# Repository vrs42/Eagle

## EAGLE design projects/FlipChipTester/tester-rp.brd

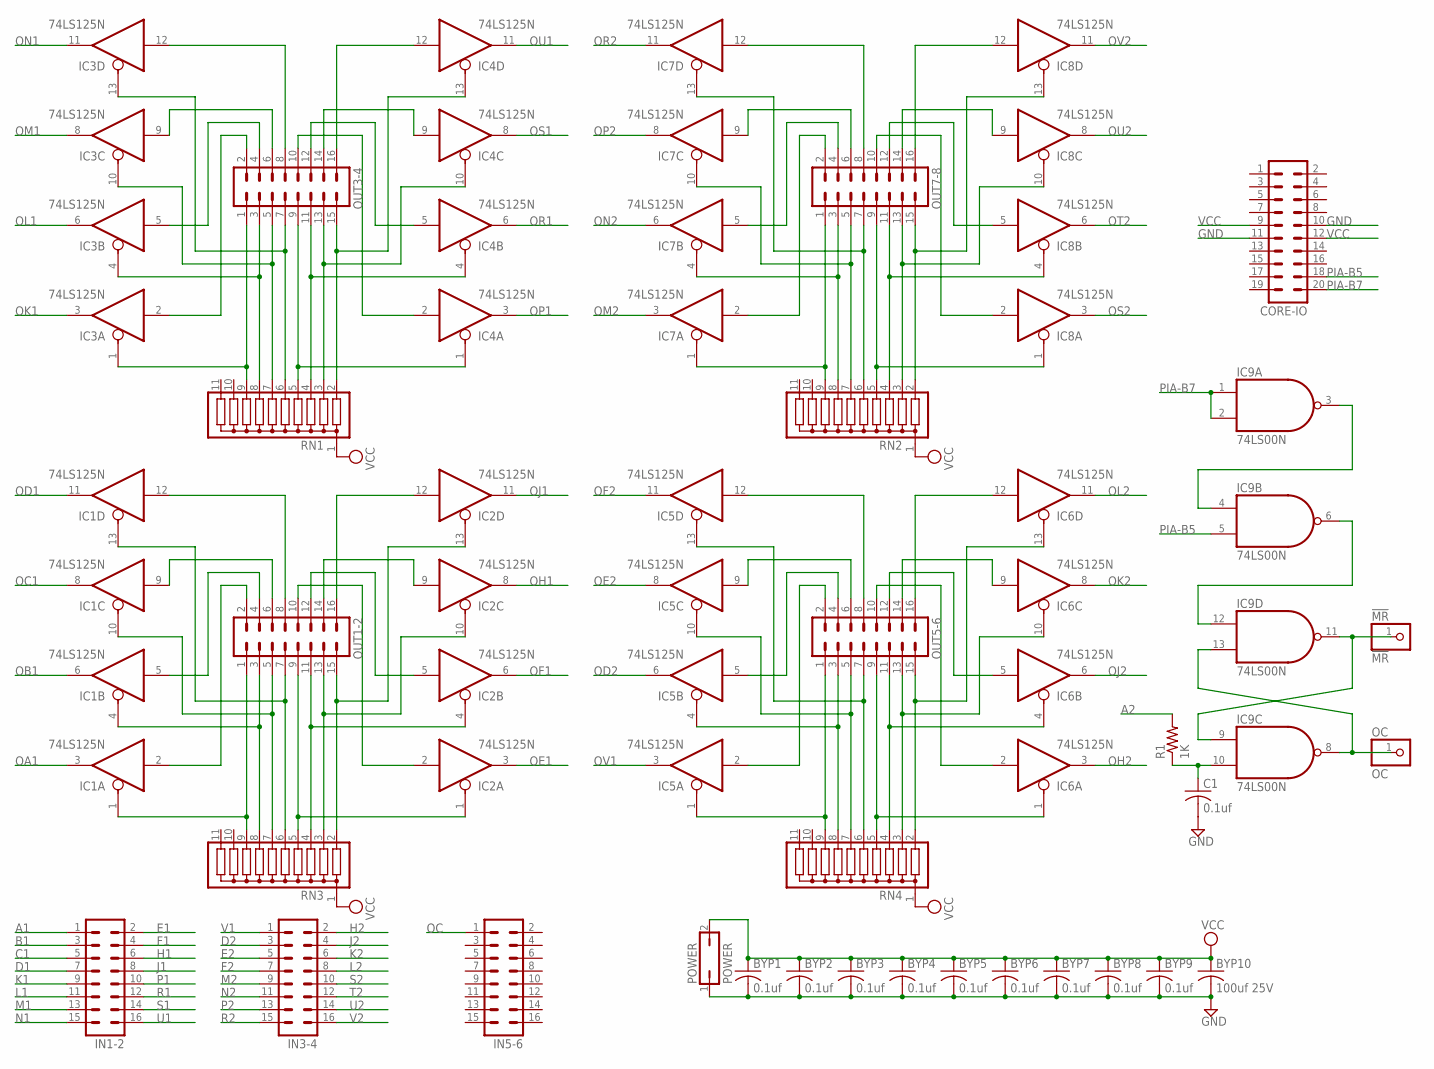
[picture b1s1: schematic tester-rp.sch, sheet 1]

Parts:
!MR: !MR; 1X01
BYP1, BYP2, BYP3, BYP4, BYP5, BYP6, BYP7, BYP8, BYP9: 0.1uf; C050-025X075
BYP10: 100uf 25V; C150-064X183
C1: 0.1uf; C050-025X075
CORE-IO: MA10-2
IC1, IC2, IC3, IC4, IC5, IC6, IC7, IC8: 74LS125N; DIL14
IC9: 74LS00N; DIL14
IN1-2, IN3-4, IN5-6: MA08-2
OC: OC; 1X01
OUT1-2, OUT3-4, OUT5-6, OUT7-8: MA08-2
POWER: POWER; JP1
R1: 1K; 0207/10
RN1, RN2, RN3, RN4: G10R; SIL11

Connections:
!MR: !MR.1, IC9.9 (I0), IC9.11 (O)
A1: IN1-2.1; also elsewhere on the board
A2: R1.2; also elsewhere on the board
B1: IN1-2.3; also elsewhere on the board
C1: IN1-2.5; also elsewhere on the board
D1: IN1-2.7; also elsewhere on the board
D2: IN3-4.3; also elsewhere on the board
E1: IN1-2.2; also elsewhere on the board
E2: IN3-4.5; also elsewhere on the board
F1: IN1-2.4; also elsewhere on the board
F2: IN3-4.7; also elsewhere on the board
GND: BYP1.2, BYP2.2, BYP3.2, BYP4.2, BYP5.2, BYP6.2, BYP7.2, BYP8.2, BYP9.2, BYP10.2, C1.2, CORE-IO.10, CORE-IO.11, IC1.7 (GND), IC2.7 (GND), IC3.7 (GND), IC4.7 (GND), IC5.7 (GND), IC6.7 (GND), IC7.7 (GND), IC8.7 (GND), IC9.7 (GND), POWER.1; also elsewhere on the board
H1: IN1-2.6; also elsewhere on the board
H2: IN3-4.2; also elsewhere on the board
J1: IN1-2.8; also elsewhere on the board
J2: IN3-4.4; also elsewhere on the board
K1: IN1-2.9; also elsewhere on the board
K2: IN3-4.6; also elsewhere on the board
L1: IN1-2.11; also elsewhere on the board
L2: IN3-4.8; also elsewhere on the board
M1: IN1-2.13; also elsewhere on the board
M2: IN3-4.9; also elsewhere on the board
N1: IN1-2.15; also elsewhere on the board
N2: IN3-4.11; also elsewhere on the board
unnamed: IC9.6 (O), IC9.12 (I0)
unnamed: IC9.3 (O), IC9.4 (I0)
unnamed: C1.1, IC9.10 (I1), R1.1
unnamed: IC1.1 (OE), OUT1-2.1, RN3.9
unnamed: IC1.4 (OE), OUT1-2.3, RN3.8
unnamed: IC1.10 (OE), OUT1-2.5, RN3.7
unnamed: IC1.13 (OE), OUT1-2.7, RN3.6
unnamed: IC1.2 (I), OUT1-2.2
unnamed: IC1.5 (I), OUT1-2.4
unnamed: IC1.9 (I), OUT1-2.6
unnamed: IC1.12 (I), OUT1-2.8
unnamed: IC5.4 (OE), OUT5-6.3, RN4.8
unnamed: IC2.10 (OE), OUT1-2.13, RN3.3
unnamed: IC2.4 (OE), OUT1-2.11, RN3.4
unnamed: IC2.1 (OE), OUT1-2.9, RN3.5
unnamed: IC2.2 (I), OUT1-2.10
unnamed: IC2.5 (I), OUT1-2.12
unnamed: IC2.9 (I), OUT1-2.14
unnamed: IC2.12 (I), OUT1-2.16
unnamed: IC5.13 (OE), OUT5-6.7, RN4.6
unnamed: IC2.13 (OE), OUT1-2.15, RN3.2
unnamed: IC5.2 (I), OUT5-6.2
unnamed: IC5.5 (I), OUT5-6.4
unnamed: IC5.9 (I), OUT5-6.6
unnamed: IC5.12 (I), OUT5-6.8
unnamed: IC6.10 (OE), OUT5-6.13, RN4.3
unnamed: IC6.4 (OE), OUT5-6.11, RN4.4
unnamed: IC6.1 (OE), OUT5-6.9, RN4.5
unnamed: IC6.2 (I), OUT5-6.10
unnamed: IC6.9 (I), OUT5-6.14
unnamed: IC6.12 (I), OUT5-6.16
unnamed: IC5.1 (OE), OUT5-6.1, RN4.9
unnamed: IC5.10 (OE), OUT5-6.5, RN4.7
unnamed: IC6.5 (I), OUT5-6.12
unnamed: IC6.13 (OE), OUT5-6.15, RN4.2
unnamed: IC3.4 (OE), OUT3-4.3, RN1.8
unnamed: IC3.13 (OE), OUT3-4.7, RN1.6
unnamed: IC3.2 (I), OUT3-4.2
unnamed: IC3.5 (I), OUT3-4.4
unnamed: IC3.9 (I), OUT3-4.6
unnamed: IC3.12 (I), OUT3-4.8
unnamed: IC4.10 (OE), OUT3-4.13, RN1.3
unnamed: IC4.4 (OE), OUT3-4.11, RN1.4
unnamed: IC4.1 (OE), OUT3-4.9, RN1.5
unnamed: IC4.2 (I), OUT3-4.10
unnamed: IC4.9 (I), OUT3-4.14
unnamed: IC4.12 (I), OUT3-4.16
unnamed: IC3.1 (OE), OUT3-4.1, RN1.9
unnamed: IC3.10 (OE), OUT3-4.5, RN1.7
unnamed: IC4.5 (I), OUT3-4.12
unnamed: IC4.13 (OE), OUT3-4.15, RN1.2
unnamed: IC7.4 (OE), OUT7-8.3, RN2.8
unnamed: IC7.13 (OE), OUT7-8.7, RN2.6
unnamed: IC7.2 (I), OUT7-8.2
unnamed: IC7.5 (I), OUT7-8.4
unnamed: IC7.9 (I), OUT7-8.6
unnamed: IC7.12 (I), OUT7-8.8
unnamed: IC8.10 (OE), OUT7-8.13, RN2.3
unnamed: IC8.4 (OE), OUT7-8.11, RN2.4
unnamed: IC8.1 (OE), OUT7-8.9, RN2.5
unnamed: IC8.2 (I), OUT7-8.10
unnamed: IC8.9 (I), OUT7-8.14
unnamed: IC8.12 (I), OUT7-8.16
unnamed: IC7.1 (OE), OUT7-8.1, RN2.9
unnamed: IC7.10 (OE), OUT7-8.5, RN2.7
unnamed: IC8.5 (I), OUT7-8.12
unnamed: IC8.13 (OE), OUT7-8.15, RN2.2
OA1: IC1.3 (O); also elsewhere on the board
OB1: IC1.6 (O); also elsewhere on the board
OC: IC9.8 (O), IC9.13 (I1), IN5-6.1, OC.1
OC1: IC1.8 (O); also elsewhere on the board
OD1: IC1.11 (O); also elsewhere on the board
OD2: IC5.6 (O); also elsewhere on the board
OE1: IC2.3 (O); also elsewhere on the board
OE2: IC5.8 (O); also elsewhere on the board
OF1: IC2.6 (O); also elsewhere on the board
OF2: IC5.11 (O); also elsewhere on the board
OH1: IC2.8 (O); also elsewhere on the board
OH2: IC6.3 (O); also elsewhere on the board
OJ1: IC2.11 (O); also elsewhere on the board
OJ2: IC6.6 (O); also elsewhere on the board
OK1: IC3.3 (O); also elsewhere on the board
OK2: IC6.8 (O); also elsewhere on the board
OL1: IC3.6 (O); also elsewhere on the board
OL2: IC6.11 (O); also elsewhere on the board
OM1: IC3.8 (O); also elsewhere on the board
OM2: IC7.3 (O); also elsewhere on the board
ON1: IC3.11 (O); also elsewhere on the board
ON2: IC7.6 (O); also elsewhere on the board
OP1: IC4.3 (O); also elsewhere on the board
OP2: IC7.8 (O); also elsewhere on the board
OR1: IC4.6 (O); also elsewhere on the board
OR2: IC7.11 (O); also elsewhere on the board
OS1: IC4.8 (O); also elsewhere on the board
OS2: IC8.3 (O); also elsewhere on the board
OT2: IC8.6 (O); also elsewhere on the board
OU1: IC4.11 (O); also elsewhere on the board
OU2: IC8.8 (O); also elsewhere on the board
OV1: IC5.3 (O); also elsewhere on the board
OV2: IC8.11 (O); also elsewhere on the board
P1: IN1-2.10; also elsewhere on the board
P2: IN3-4.13; also elsewhere on the board
PIA-B5: CORE-IO.18, IC9.5 (I1)
PIA-B7: CORE-IO.20, IC9.1 (I0), IC9.2 (I1)
R1: IN1-2.12; also elsewhere on the board
R2: IN3-4.15; also elsewhere on the board
S1: IN1-2.14; also elsewhere on the board
S2: IN3-4.10; also elsewhere on the board
T2: IN3-4.12; also elsewhere on the board
U1: IN1-2.16; also elsewhere on the board
U2: IN3-4.14; also elsewhere on the board
V1: IN3-4.1; also elsewhere on the board
V2: IN3-4.16; also elsewhere on the board
VCC: BYP1.1, BYP2.1, BYP3.1, BYP4.1, BYP5.1, BYP6.1, BYP7.1, BYP8.1, BYP9.1, BYP10.1, CORE-IO.9, CORE-IO.12, IC1.14 (VCC), IC2.14 (VCC), IC3.14 (VCC), IC4.14 (VCC), IC5.14 (VCC), IC6.14 (VCC), IC7.14 (VCC), IC8.14 (VCC), IC9.14 (VCC), POWER.2, RN1.1, RN2.1, RN3.1, RN4.1; also elsewhere on the board

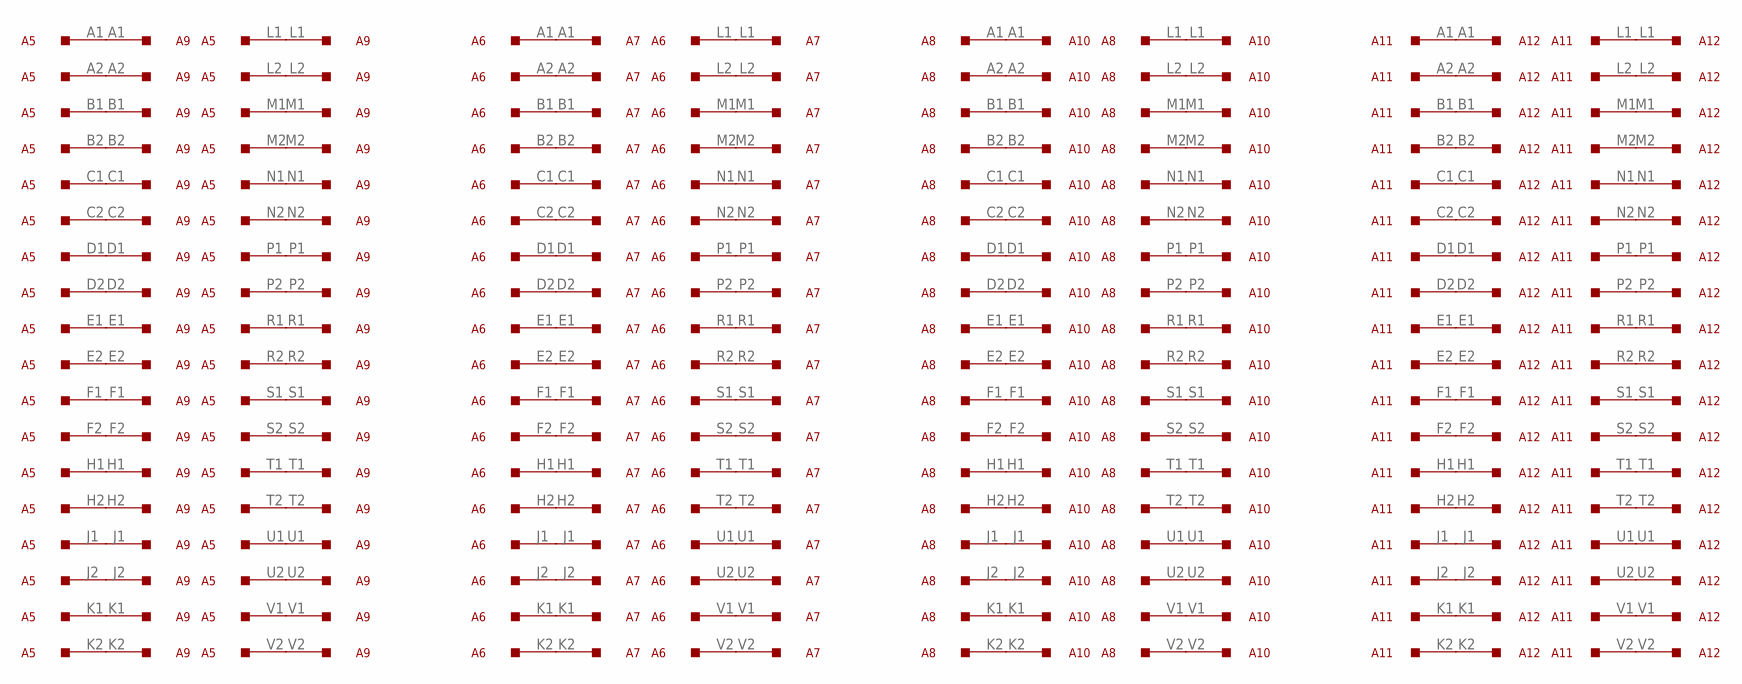
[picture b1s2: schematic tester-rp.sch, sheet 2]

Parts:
A5, A6, A7, A8, A9, A10, A11, A12: M916; H807

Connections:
unnamed: A5.L1, A9.L1
unnamed: A5.L2, A9.L2
unnamed: A5.M1, A9.M1
unnamed: A5.M2, A9.M2
unnamed: A5.N1, A9.N1
unnamed: A5.N2, A9.N2
unnamed: A5.P1, A9.P1
unnamed: A5.P2, A9.P2
unnamed: A5.R1, A9.R1
unnamed: A5.R2, A9.R2
unnamed: A5.S1, A9.S1
unnamed: A5.S2, A9.S2
unnamed: A5.T1, A9.T1
unnamed: A5.T2, A9.T2
unnamed: A5.U1, A9.U1
unnamed: A5.U2, A9.U2
unnamed: A5.V1, A9.V1
unnamed: A5.V2, A9.V2
unnamed: A5.A1, A9.A1
unnamed: A5.A2, A9.A2
unnamed: A5.B1, A9.B1
unnamed: A5.B2, A9.B2
unnamed: A5.C1, A9.C1
unnamed: A5.C2, A9.C2
unnamed: A5.D1, A9.D1
unnamed: A5.D2, A9.D2
unnamed: A5.E1, A9.E1
unnamed: A5.E2, A9.E2
unnamed: A5.F1, A9.F1
unnamed: A5.F2, A9.F2
unnamed: A5.H1, A9.H1
unnamed: A5.H2, A9.H2
unnamed: A5.J1, A9.J1
unnamed: A5.J2, A9.J2
unnamed: A5.K1, A9.K1
unnamed: A5.K2, A9.K2
unnamed: A6.L1, A7.L1
unnamed: A6.L2, A7.L2
unnamed: A6.M1, A7.M1
unnamed: A6.M2, A7.M2
unnamed: A6.N1, A7.N1
unnamed: A6.N2, A7.N2
unnamed: A6.P1, A7.P1
unnamed: A6.P2, A7.P2
unnamed: A6.R1, A7.R1
unnamed: A6.R2, A7.R2
unnamed: A6.S1, A7.S1
unnamed: A6.S2, A7.S2
unnamed: A6.T1, A7.T1
unnamed: A6.T2, A7.T2
unnamed: A6.U1, A7.U1
unnamed: A6.U2, A7.U2
unnamed: A6.V1, A7.V1
unnamed: A6.V2, A7.V2
unnamed: A6.A1, A7.A1
unnamed: A6.A2, A7.A2
unnamed: A6.B1, A7.B1
unnamed: A6.B2, A7.B2
unnamed: A6.C1, A7.C1
unnamed: A6.C2, A7.C2
unnamed: A6.D1, A7.D1
unnamed: A6.D2, A7.D2
unnamed: A6.E1, A7.E1
unnamed: A6.E2, A7.E2
unnamed: A6.F1, A7.F1
unnamed: A6.F2, A7.F2
unnamed: A6.H1, A7.H1
unnamed: A6.H2, A7.H2
unnamed: A6.J1, A7.J1
unnamed: A6.J2, A7.J2
unnamed: A6.K1, A7.K1
unnamed: A6.K2, A7.K2
unnamed: A8.L1, A10.L1
unnamed: A8.L2, A10.L2
unnamed: A8.M1, A10.M1
unnamed: A8.M2, A10.M2
unnamed: A8.N1, A10.N1
unnamed: A8.N2, A10.N2
unnamed: A8.P1, A10.P1
unnamed: A8.P2, A10.P2
unnamed: A8.R1, A10.R1
unnamed: A8.R2, A10.R2
unnamed: A8.S1, A10.S1
unnamed: A8.S2, A10.S2
unnamed: A8.T1, A10.T1
unnamed: A8.T2, A10.T2
unnamed: A8.U1, A10.U1
unnamed: A8.U2, A10.U2
unnamed: A8.V1, A10.V1
unnamed: A8.V2, A10.V2
unnamed: A8.A1, A10.A1
unnamed: A8.A2, A10.A2
unnamed: A8.B1, A10.B1
unnamed: A8.B2, A10.B2
unnamed: A8.C1, A10.C1
unnamed: A8.C2, A10.C2
unnamed: A8.D1, A10.D1
unnamed: A8.D2, A10.D2
unnamed: A8.E1, A10.E1
unnamed: A8.E2, A10.E2
unnamed: A8.F1, A10.F1
unnamed: A8.F2, A10.F2
unnamed: A8.H1, A10.H1
unnamed: A8.H2, A10.H2
unnamed: A8.J1, A10.J1
unnamed: A8.J2, A10.J2
unnamed: A8.K1, A10.K1
unnamed: A8.K2, A10.K2
unnamed: A11.L1, A12.L1
unnamed: A11.L2, A12.L2
unnamed: A11.M1, A12.M1
unnamed: A11.M2, A12.M2
unnamed: A11.N1, A12.N1
unnamed: A11.N2, A12.N2
unnamed: A11.P1, A12.P1
unnamed: A11.P2, A12.P2
unnamed: A11.R1, A12.R1
unnamed: A11.R2, A12.R2
unnamed: A11.S1, A12.S1
unnamed: A11.S2, A12.S2
unnamed: A11.T1, A12.T1
unnamed: A11.T2, A12.T2
unnamed: A11.U1, A12.U1
unnamed: A11.U2, A12.U2
unnamed: A11.V1, A12.V1
unnamed: A11.V2, A12.V2
unnamed: A11.A1, A12.A1
unnamed: A11.A2, A12.A2
unnamed: A11.B1, A12.B1
unnamed: A11.B2, A12.B2
unnamed: A11.C1, A12.C1
unnamed: A11.C2, A12.C2
unnamed: A11.D1, A12.D1
unnamed: A11.D2, A12.D2
unnamed: A11.E1, A12.E1
unnamed: A11.E2, A12.E2
unnamed: A11.F1, A12.F1
unnamed: A11.F2, A12.F2
unnamed: A11.H1, A12.H1
unnamed: A11.H2, A12.H2
unnamed: A11.J1, A12.J1
unnamed: A11.J2, A12.J2
unnamed: A11.K1, A12.K1
unnamed: A11.K2, A12.K2

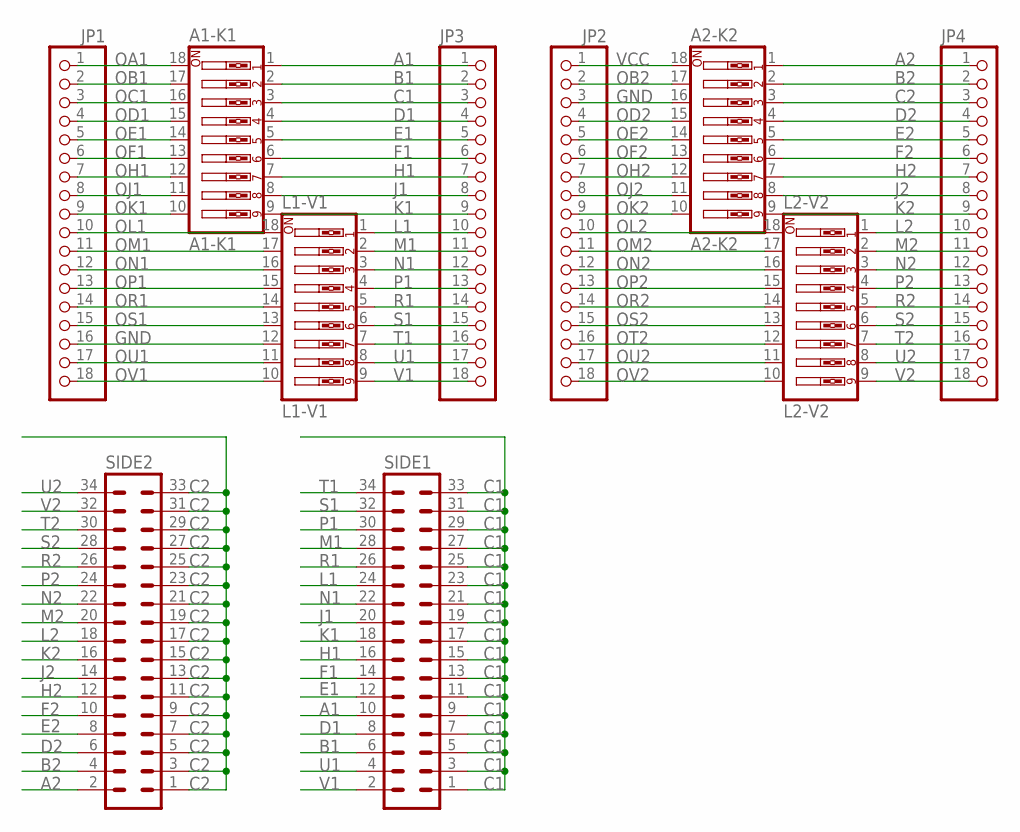
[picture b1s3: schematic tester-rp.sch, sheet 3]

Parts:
A1-K1: A1-K1; EDG-09
A2-K2: A2-K2; EDG-09
JP1, JP2, JP3, JP4: PINHD-1X18; 1X18
L1-V1: L1-V1; EDG-09
L2-V2: L2-V2; EDG-09
SIDE1, SIDE2: MA17-2

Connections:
A1: A1-K1.1, JP3.1, SIDE1.10; also elsewhere on the board
A2: A2-K2.1, JP4.1, SIDE2.2; also elsewhere on the board
B1: A1-K1.2, JP3.2, SIDE1.6; also elsewhere on the board
B2: A2-K2.2, JP4.2, SIDE2.4
C1: A1-K1.3, JP3.3, SIDE1.1, SIDE1.3, SIDE1.5, SIDE1.7, SIDE1.9, SIDE1.11, SIDE1.13, SIDE1.15, SIDE1.17, SIDE1.19, SIDE1.21, SIDE1.23, SIDE1.25, SIDE1.27, SIDE1.29, SIDE1.31, SIDE1.33; also elsewhere on the board
C2: A2-K2.3, JP4.3, SIDE2.1, SIDE2.3, SIDE2.5, SIDE2.7, SIDE2.9, SIDE2.11, SIDE2.13, SIDE2.15, SIDE2.17, SIDE2.19, SIDE2.21, SIDE2.23, SIDE2.25, SIDE2.27, SIDE2.29, SIDE2.31, SIDE2.33
D1: A1-K1.4, JP3.4, SIDE1.8; also elsewhere on the board
D2: A2-K2.4, JP4.4, SIDE2.6; also elsewhere on the board
E1: A1-K1.5, JP3.5, SIDE1.12; also elsewhere on the board
E2: A2-K2.5, JP4.5, SIDE2.8; also elsewhere on the board
F1: A1-K1.6, JP3.6, SIDE1.14; also elsewhere on the board
F2: A2-K2.6, JP4.6, SIDE2.10; also elsewhere on the board
GND: A2-K2.16, JP1.16, JP2.3, L1-V1.12; also elsewhere on the board
H1: A1-K1.7, JP3.7, SIDE1.16; also elsewhere on the board
H2: A2-K2.7, JP4.7, SIDE2.12; also elsewhere on the board
J1: A1-K1.8, JP3.8, SIDE1.20; also elsewhere on the board
J2: A2-K2.8, JP4.8, SIDE2.14; also elsewhere on the board
K1: A1-K1.9, JP3.9, SIDE1.18; also elsewhere on the board
K2: A2-K2.9, JP4.9, SIDE2.16; also elsewhere on the board
L1: JP3.10, L1-V1.1, SIDE1.24; also elsewhere on the board
L2: JP4.10, L2-V2.1, SIDE2.18; also elsewhere on the board
M1: JP3.11, L1-V1.2, SIDE1.28; also elsewhere on the board
M2: JP4.11, L2-V2.2, SIDE2.20; also elsewhere on the board
N1: JP3.12, L1-V1.3, SIDE1.22; also elsewhere on the board
N2: JP4.12, L2-V2.3, SIDE2.22; also elsewhere on the board
OA1: A1-K1.18, JP1.1; also elsewhere on the board
OB1: A1-K1.17, JP1.2; also elsewhere on the board
OB2: A2-K2.17, JP2.2
OC1: A1-K1.16, JP1.3; also elsewhere on the board
OD1: A1-K1.15, JP1.4; also elsewhere on the board
OD2: A2-K2.15, JP2.4; also elsewhere on the board
OE1: A1-K1.14, JP1.5; also elsewhere on the board
OE2: A2-K2.14, JP2.5; also elsewhere on the board
OF1: A1-K1.13, JP1.6; also elsewhere on the board
OF2: A2-K2.13, JP2.6; also elsewhere on the board
OH1: A1-K1.12, JP1.7; also elsewhere on the board
OH2: A2-K2.12, JP2.7; also elsewhere on the board
OJ1: A1-K1.11, JP1.8; also elsewhere on the board
OJ2: A2-K2.11, JP2.8; also elsewhere on the board
OK1: A1-K1.10, JP1.9; also elsewhere on the board
OK2: A2-K2.10, JP2.9; also elsewhere on the board
OL1: JP1.10, L1-V1.18; also elsewhere on the board
OL2: JP2.10, L2-V2.18; also elsewhere on the board
OM1: JP1.11, L1-V1.17; also elsewhere on the board
OM2: JP2.11, L2-V2.17; also elsewhere on the board
ON1: JP1.12, L1-V1.16; also elsewhere on the board
ON2: JP2.12, L2-V2.16; also elsewhere on the board
OP1: JP1.13, L1-V1.15; also elsewhere on the board
OP2: JP2.13, L2-V2.15; also elsewhere on the board
OR1: JP1.14, L1-V1.14; also elsewhere on the board
OR2: JP2.14, L2-V2.14; also elsewhere on the board
OS1: JP1.15, L1-V1.13; also elsewhere on the board
OS2: JP2.15, L2-V2.13; also elsewhere on the board
OT2: JP2.16, L2-V2.12; also elsewhere on the board
OU1: JP1.17, L1-V1.11; also elsewhere on the board
OU2: JP2.17, L2-V2.11; also elsewhere on the board
OV1: JP1.18, L1-V1.10; also elsewhere on the board
OV2: JP2.18, L2-V2.10; also elsewhere on the board
P1: JP3.13, L1-V1.4, SIDE1.30; also elsewhere on the board
P2: JP4.13, L2-V2.4, SIDE2.24; also elsewhere on the board
R1: JP3.14, L1-V1.5, SIDE1.26; also elsewhere on the board
R2: JP4.14, L2-V2.5, SIDE2.26; also elsewhere on the board
S1: JP3.15, L1-V1.6, SIDE1.32; also elsewhere on the board
S2: JP4.15, L2-V2.6, SIDE2.28; also elsewhere on the board
T1: JP3.16, L1-V1.7, SIDE1.34
T2: JP4.16, L2-V2.7, SIDE2.30; also elsewhere on the board
U1: JP3.17, L1-V1.8, SIDE1.4; also elsewhere on the board
U2: JP4.17, L2-V2.8, SIDE2.34; also elsewhere on the board
V1: JP3.18, L1-V1.9, SIDE1.2; also elsewhere on the board
V2: JP4.18, L2-V2.9, SIDE2.32; also elsewhere on the board
VCC: A2-K2.18, JP2.1; also elsewhere on the board

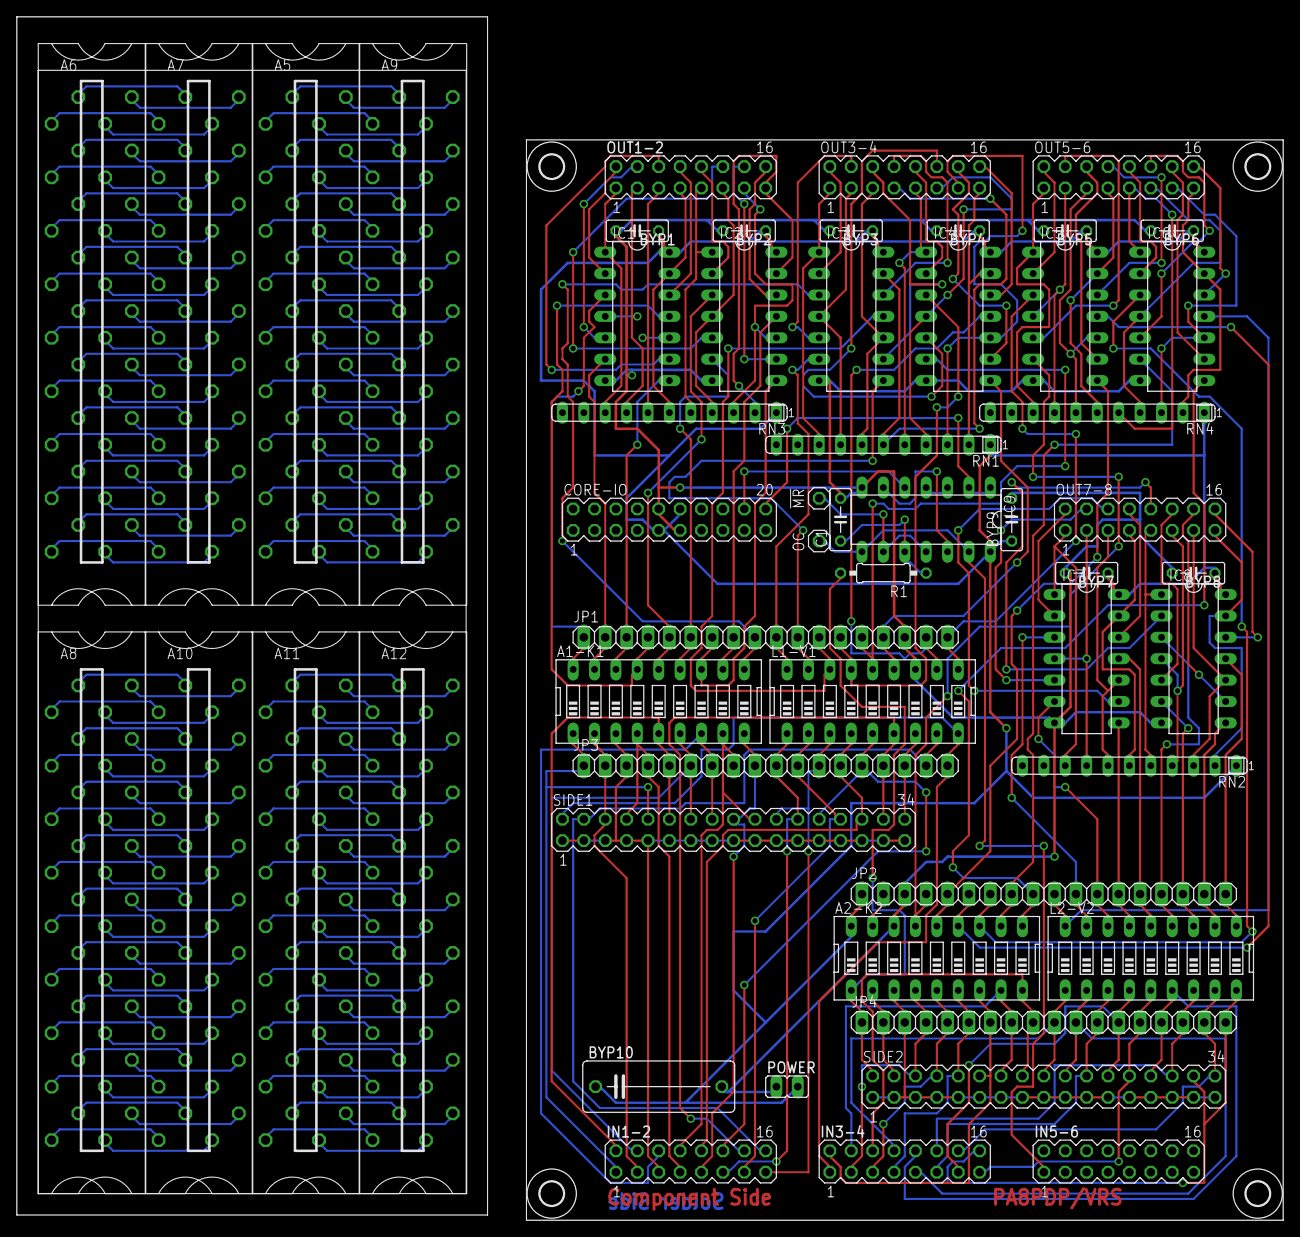
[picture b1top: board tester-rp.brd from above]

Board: 2 copper layers, 89.8 x 128.2 mm, 59 parts (0 on the bottom side), 286 nets.

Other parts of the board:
U$1, U$2, U$3, U$4: 2,8
U$5: CBLOCK

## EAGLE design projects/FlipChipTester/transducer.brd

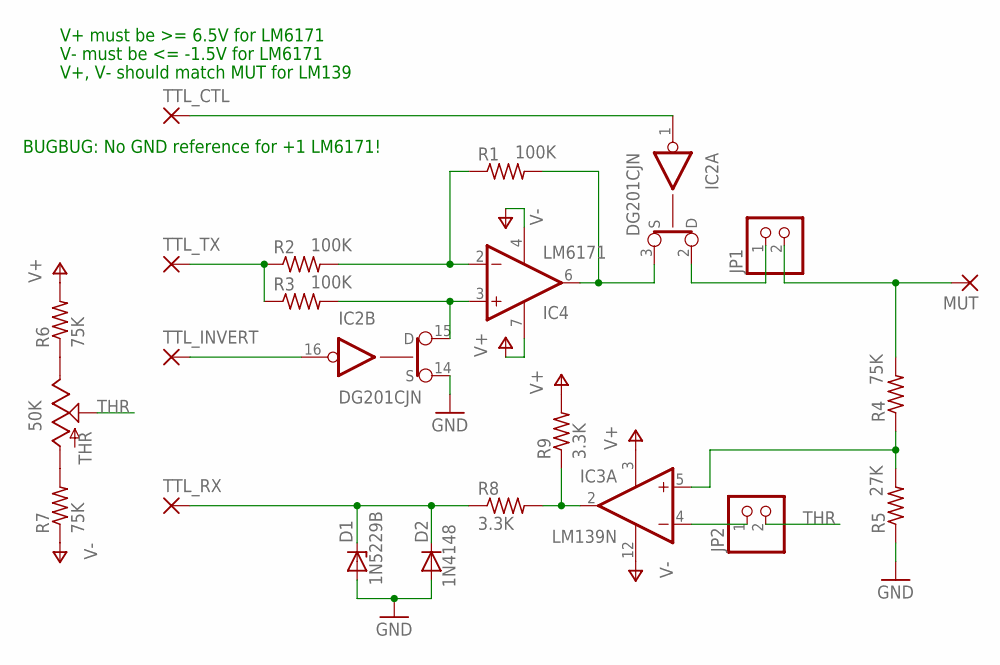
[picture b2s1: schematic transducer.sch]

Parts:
D1: 1N5229B; DO35Z10
D2: 1N4148; DO35-10
IC2: DG201CJN; DIL16
IC3: LM139N; DIL14
IC4: LM6171; DIL08
JP1, JP2: PINHD-1X2; 1X02
MUT: 1,6/0,9
R1, R2, R3: 100K; 0207/10
R4, R6, R7: 75K; 0207/10
R5: 27K; 0207/10
R8, R9: 3.3K; 0207/10
THR: 50K; SP19L
TTL_CTL: 1,6/0,9
TTL_INVERT: 1,6/0,9
TTL_RX: 1,6/0,9
TTL_TX: 1,6/0,9

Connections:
GND: D1.A, D2.A, IC2.5 (GND), IC2.14 (S), R5.1
unnamed: R2.1, R3.1, TTL_TX.1
unnamed: IC2.15 (D), IC4.3 (+IN), R3.2
unnamed: IC4.2 (-IN), R1.1, R2.2
unnamed: IC2.3 (S), IC4.6 (OUT), R1.2
unnamed: IC2.2 (D), JP1.1
unnamed: JP1.2, MUT.1, R4.2
unnamed: IC3.5 (+IN), R4.1, R5.2
unnamed: IC3.4 (-IN), JP2.1
unnamed: IC3.2 (OUT), R8.2, R9.1
unnamed: IC2.16 (IN), TTL_INVERT.1
unnamed: IC2.1 (IN), TTL_CTL.1
unnamed: D1.C, D2.C, R8.1, TTL_RX.1
unnamed: R6.1, THR.E
unnamed: R7.2, THR.A
THR: JP2.2, THR.S
V+: IC2.13 (V+), IC3.3 (V+), IC4.7 (V+), R6.2, R9.2
V-: IC2.4 (V-), IC3.12 (GND), IC4.4 (V-), R7.1

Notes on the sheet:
V+ must be >= 6.5V for LM6171
V+, V- should match MUT for LM139
V- must be <= -1.5V for LM6171
BUGBUG: No GND reference for +1 LM6171!

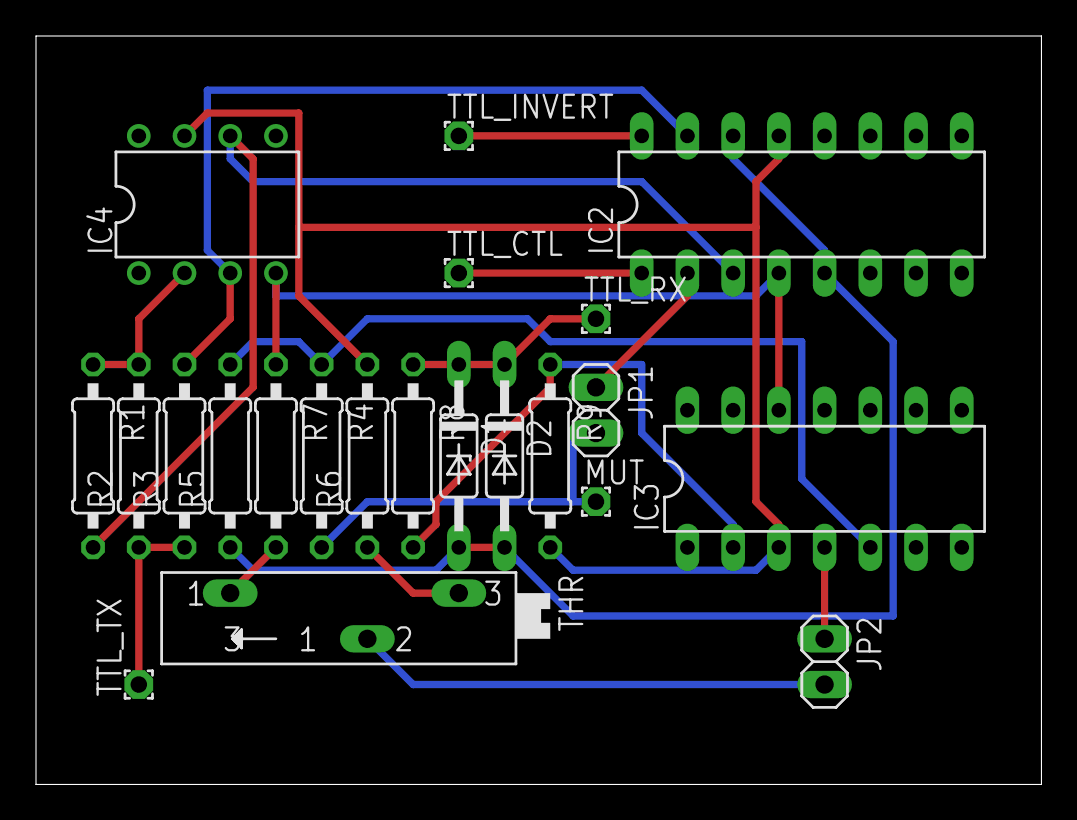
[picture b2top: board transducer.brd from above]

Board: 2 copper layers, 55.9 x 41.6 mm, 22 parts (0 on the bottom side), 18 nets.

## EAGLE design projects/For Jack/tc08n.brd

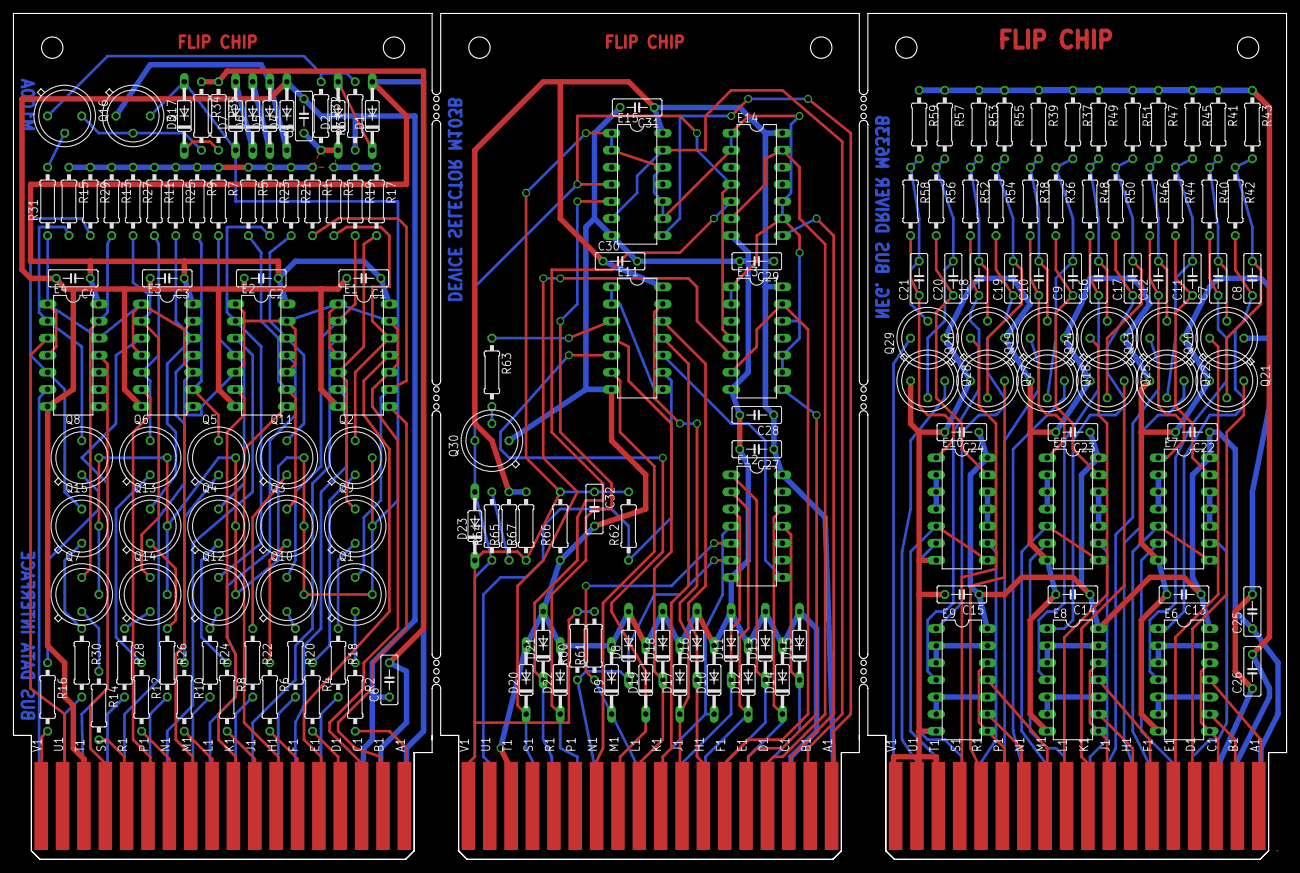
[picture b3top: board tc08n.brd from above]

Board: 2 copper layers, 189.2 x 125.7 mm, 172 parts (0 on the bottom side), 176 nets.

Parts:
C1, C2, C3, C4, C5, C6, C27, C28, C29, C30, C31, C32: .01uf; C050-025X075
C7, C8, C9, C10, C11, C12, C16, C17, C18, C19, C20, C21: 15pF; C050-025X075
C13, C14, C15, C22, C23, C24, C25, C26: .01uF; C050-025X075
D1, D2, D4, D5, D6, D7: 1N914; DO35-10
D3, D8, D9, D10, D11, D12, D13, D14, D15, D16, D17, D18, D19, D20, D21, D22, D23: 1N4154; DO35-10
E1, E2, E3, E4, E11: 7400N; DIL14
E5, E6, E7, E8, E9, E10: 7402N; DIL14
E12: 7430N; DIL14
E13, E14, E15: 74H40N; DIL14
E$1: DECPROTO
Q1, Q2, Q3, Q4, Q5, Q6, Q7, Q8, Q9, Q10, Q11, Q12, Q13, Q14, Q15: PN3569; TO5
Q16, Q17: MPS6534; TO5
Q18, Q19, Q20, Q21, Q22, Q23, Q24, Q25, Q26, Q27, Q28, Q29: PN3640; TO39
Q30: PN3569; TO39
R1, R3, R5, R7, R9, R11, R13, R15, R17, R19, R21, R23, R25, R27, R29, R35: 4700; 0207/10
R2, R4, R6, R8, R10, R12, R14, R16, R18, R20, R22, R24, R26, R28, R30: 470; 0207/10
R31: 1000; 0207/10
R32: 100; 0207/10
R33: 220; 0207/10
R34: 2200; 0207/10
R36, R38, R40, R42, R44, R46, R48, R50, R52, R54, R56, R58: 1k; 0207/10
R37, R39, R41, R43, R45, R47, R49, R51, R53, R55, R57, R59: 5.6K; 0207/10
R60, R61, R62: 8.2K; 0207/10
R63, R64, R65, R66: 750; 0207/10
R67: 330; 0207/10
U$1, U$4, U$8: EDGE-CON2
U$5: FLIPCHIP

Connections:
+2V: Q16.1, R32.1, R33.2
+3V: C5.1, D2.C, R1.1, R3.1, R5.1, R7.1, R9.1, R11.1, R13.1, R15.1, R17.1, R19.1, R21.1, R23.1, R25.1, R27.1, R29.1, R32.2
+3V3: C32.1, D23.C, E13.1, E13.2, E13.9, E13.10, E13.12, E14.1, E14.2, E14.9, E14.10, E14.12, E15.1, E15.2, E15.9, E15.10, E15.12, R60.2, R61.2, R62.2, R66.2, R67.1, U$8.V1
-15V: C6.2, R34.1, R35.1, U$1.B2
-15V1: C26.2, R37.1, R39.1, R41.1, R43.1, R45.1, R47.1, R49.1, R51.1, R53.1, R55.1, R57.1, R59.1, U$4.B2
A1: E15.8, U$8.A1
B1: E15.6, E15.13, U$8.B1
C1: E14.8, U$8.C1
D1: E14.6, E14.13, U$8.D1
D2: D15.C, E12.11, U$8.D2
E1: E13.8, U$8.E1
E2: D14.C, E12.12, U$8.E2
F1: E13.6, E13.13, U$8.F1
F2: D13.C, E12.1, U$8.F2
GND: C1.2, C2.2, C3.2, C4.2, C5.2, C6.1, D4.A, E1.7, E2.7, E3.7, E4.7, R33.1, U$1.C2, U$1.T1
GND1: C13.2, C14.2, C15.2, C22.2, C23.2, C24.2, C25.2, C26.1, E5.7, E6.7, E7.7, E8.7, E9.7, E10.7, Q18.1, Q19.1, Q20.1, Q21.1, Q22.1, Q23.1, Q24.1, Q25.1, Q26.1, Q27.1, Q28.1, Q29.1, U$4.C2, U$4.T1, U$4.U1, U$4.V1
GND2: C27.2, C28.2, C29.2, C30.2, C31.2, C32.2, D8.A, D9.A, D10.A, D11.A, D12.A, D13.A, D14.A, D15.A, D16.A, D17.A, D18.A, D19.A, D20.A, D21.A, D22.A, E11.7, E12.7, E13.7, E14.7, E15.7, Q30.1, R66.1, U$8.C2, U$8.T1
H1: D16.C, E11.12, U$8.H1
H2: D12.C, E12.2, U$8.H2
J1: D17.C, E11.13, U$8.J1
J2: D11.C, E12.3, U$8.J2
K1: E11.11, U$8.K1
K2: D10.C, E12.4, U$8.K2
L1: D18.C, E11.4, U$8.L1
L2: D9.C, E12.5, R61.1, U$8.L2
M1: D19.C, E11.5, U$8.M1
N1: E11.6, U$8.N1
N2: D8.C, E12.6, R60.1, U$8.N2
unnamed: Q1.1, R2.1
unnamed: E1.9, Q1.3, R1.2
unnamed: E5.10, E5.11, E5.12
unnamed: E1.1, E1.4, E1.10, E1.13, E2.1, E2.5, E2.10, E2.13, E3.1, E3.4, E3.10, E3.13, E4.1, E4.4, E4.12, R31.1, U$1.C1
unnamed: E1.12, Q2.3, R3.2
unnamed: E1.8, U$1.B1
unnamed: Q2.1, R4.1
unnamed: R4.2, U$1.D1
unnamed: E1.11, U$1.E1
unnamed: R6.2, U$1.F1
unnamed: Q3.1, R6.1
unnamed: E2.9, Q3.3, R5.2
unnamed: E2.8, U$1.H1
unnamed: R8.2, U$1.J1
unnamed: Q4.1, R8.1
unnamed: E2.4, Q4.3, R7.2
unnamed: E2.6, U$1.K1
unnamed: R10.2, U$1.L1
unnamed: E3.8, U$1.M1
unnamed: E3.9, Q5.3, R9.2
unnamed: Q5.1, R10.1
unnamed: D3.A, D7.C, Q1.2, Q2.2, Q3.2, Q4.2, Q5.2, Q6.2, Q7.2, Q8.2, Q9.2, Q10.2, Q11.2, Q12.2, Q13.2, Q14.2, Q15.2, Q17.3
unnamed: R12.2, U$1.N1
unnamed: Q6.1, R12.1
unnamed: E3.5, Q6.3, R11.2
unnamed: E3.6, U$1.P1
unnamed: E4.11, U$1.S1
unnamed: Q7.1, R14.1
unnamed: R14.2, U$1.R1
unnamed: E4.13, Q7.3, R13.2
unnamed: E4.3, U$1.U1
unnamed: R16.2, U$1.V1
unnamed: R2.2, U$1.A1
unnamed: E4.2, Q8.3, R15.2
unnamed: R18.2, U$1.E2
unnamed: E1.6, U$1.F2
unnamed: R20.2, U$1.H2
unnamed: Q8.1, R16.1
unnamed: Q9.1, R18.1
unnamed: E1.5, Q9.3, R17.2
unnamed: E1.3, U$1.J2
unnamed: R22.2, U$1.K2
unnamed: E1.2, Q10.3, R19.2
unnamed: Q10.1, R20.1
unnamed: Q11.1, R22.1
unnamed: E2.12, Q11.3, R21.2
unnamed: E2.11, U$1.L2
unnamed: R24.2, U$1.M2
unnamed: Q12.1, R24.1
unnamed: E2.3, U$1.N2
unnamed: E2.2, Q12.3, R23.2
unnamed: R26.2, U$1.P2
unnamed: E3.11, U$1.R2
unnamed: E3.12, Q13.3, R25.2
unnamed: R28.2, U$1.S2
unnamed: E3.3, U$1.T2
unnamed: R30.2, U$1.U2
unnamed: Q13.1, R26.1
unnamed: Q14.1, R28.1
unnamed: E3.2, Q14.3, R27.2
unnamed: E4.6, U$1.V2
unnamed: D1.C, D2.A
unnamed: E4.5, Q15.3, R29.2
unnamed: Q15.1, R30.1
unnamed: D3.C, R35.2
unnamed: D5.C, D6.A
unnamed: D6.C, D7.A
unnamed: Q16.2, R31.2
unnamed: Q16.3, Q17.2, R34.2
unnamed: D4.C, D5.A, Q17.1
unnamed: C9.1, E5.13, R36.2
unnamed: C9.2, Q18.2, R36.1, R37.2
unnamed: E5.2, E5.3, E5.4
unnamed: C10.1, E5.1, R38.2
unnamed: C10.2, Q19.2, R38.1, R39.2
unnamed: E5.5, E5.8, U$4.M2
unnamed: E5.9, U$4.K2
unnamed: E5.6, U$4.L2
unnamed: Q19.3, U$4.P2
unnamed: Q18.3, U$4.N2
unnamed: E6.5, E6.6, E6.10
unnamed: C7.1, E6.4, R40.2
unnamed: C7.2, Q20.2, R40.1, R41.2
unnamed: E6.2, E6.3, E6.13
unnamed: C8.1, E6.1, R42.2
unnamed: C8.2, Q21.2, R42.1, R43.2
unnamed: E6.8, E6.12, U$4.C1
unnamed: E6.9, U$4.B1
unnamed: E6.11, U$4.A1
unnamed: Q21.3, U$4.D1
unnamed: Q20.3, U$4.E1
unnamed: E7.10, E7.11, E7.12
unnamed: C11.1, E7.13, R44.2
unnamed: C11.2, Q22.2, R44.1, R45.2
unnamed: E7.2, E7.3, E7.4
unnamed: C12.1, E7.1, R46.2
unnamed: C12.2, Q23.2, R46.1, R47.2
unnamed: E7.5, E7.8, U$4.F2
unnamed: E7.9, U$4.D2
unnamed: E7.6, U$4.E2
unnamed: Q23.3, U$4.J2
unnamed: Q22.3, U$4.H2
unnamed: E8.5, E8.6, E8.10
unnamed: C16.1, E8.4, R48.2
unnamed: C16.2, Q24.2, R48.1, R49.2
unnamed: E8.2, E8.3, E8.13
unnamed: C17.1, E8.1, R50.2
unnamed: C17.2, Q25.2, R50.1, R51.2
unnamed: E8.8, E8.12, U$4.J1
unnamed: E8.9, U$4.H1
unnamed: E8.11, U$4.F1
unnamed: Q25.3, U$4.K1
unnamed: Q24.3, U$4.L1
unnamed: E9.5, E9.6, E9.10
unnamed: C18.1, E9.4, R52.2
unnamed: C18.2, Q26.2, R52.1, R53.2
unnamed: E9.2, E9.3, E9.13
unnamed: C19.1, E9.1, R54.2
unnamed: C19.2, Q27.2, R54.1, R55.2
unnamed: E9.8, E9.12, U$4.P1
unnamed: E9.9, U$4.N1
unnamed: E9.11, U$4.M1
unnamed: Q27.3, U$4.R1
unnamed: Q26.3, U$4.S1
unnamed: E10.10, E10.11, E10.12
unnamed: C20.1, E10.13, R56.2
unnamed: C20.2, Q28.2, R56.1, R57.2
unnamed: E10.2, E10.3, E10.4
unnamed: C21.1, E10.1, R58.2
unnamed: C21.2, Q29.2, R58.1, R59.2
unnamed: E10.5, E10.8, U$4.T2
unnamed: E10.9, U$4.R2
unnamed: E10.6, U$4.S2
unnamed: Q29.3, U$4.V2
unnamed: Q28.3, U$4.U2
unnamed: E11.10, E12.8
unnamed: E11.1, E11.2, E11.8
unnamed: E11.3, R63.1
unnamed: Q30.2, R63.2
unnamed: R64.2, R65.1
P2: D22.C, E15.5, U$8.P2
R2: D21.C, E14.5, U$8.R2
S2: D20.C, E13.5, U$8.S2
U2: E11.9, R62.1, U$8.U2
V2: D23.A, E13.4, E14.4, E15.4, Q30.3, R64.1, U$8.V2
VCC: C1.1, C2.1, C3.1, C4.1, D1.A, E1.14, E2.14, E3.14, E4.14, U$1.A2
VCC1: C13.1, C14.1, C15.1, C22.1, C23.1, C24.1, C25.1, E5.14, E6.14, E7.14, E8.14, E9.14, E10.14, U$4.A2
VCC3: C27.1, C28.1, C29.1, C30.1, C31.1, E11.14, E12.14, E13.14, E14.14, E15.14, R65.2, R67.2, U$8.A2
